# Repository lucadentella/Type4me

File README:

Type4Me

USB keyboard emulator based on PIC18f14k50.
It allows to automatically type repetitive words (passwords...)
Includes a C# GUI.

Project description on my blog:
http://www.lucadentella.it/category/type4me/

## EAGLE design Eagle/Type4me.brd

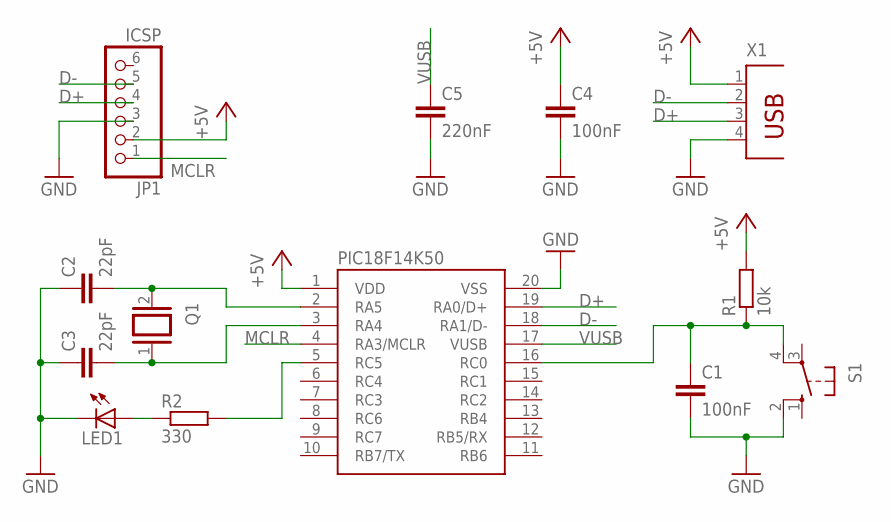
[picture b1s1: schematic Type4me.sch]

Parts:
C1, C4: 100nF; C050-030X075
C2, C3: 22pF; C025-030X050
C5: 220nF; C050-030X075
JP1: ICSP; 1X06
LED1: LED5MM
Q1: XTAL/S; QS
R1: 10k; 0207/12
R2: 330; 0207/12
S1: 10-XX; B3F-10XX
U$1: PIC18F14K50; DIP-20
X1: PN61729

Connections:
+5V: C4.1, JP1.2, R1.2, U$1.1 (VDD), X1.1
D+: JP1.4, U$1.19 (RA0/D+), X1.3
D-: JP1.5, U$1.18 (RA1/D-), X1.2
GND: C1.2, C2.1, C3.1, C4.2, C5.2, JP1.3, LED1.K (C), S1.2 (S1), U$1.20 (VSS), X1.4
MCLR: JP1.1, U$1.4 (RA3/MCLR)
unnamed: C2.2, Q1.2, U$1.2 (RA5)
unnamed: C3.2, Q1.1, U$1.3 (RA4)
unnamed: C1.1, R1.1, S1.4 (P1), U$1.16 (RC0)
unnamed: R2.2, U$1.5 (RC5)
unnamed: LED1.A, R2.1
VUSB: C5.1, U$1.17 (VUSB)

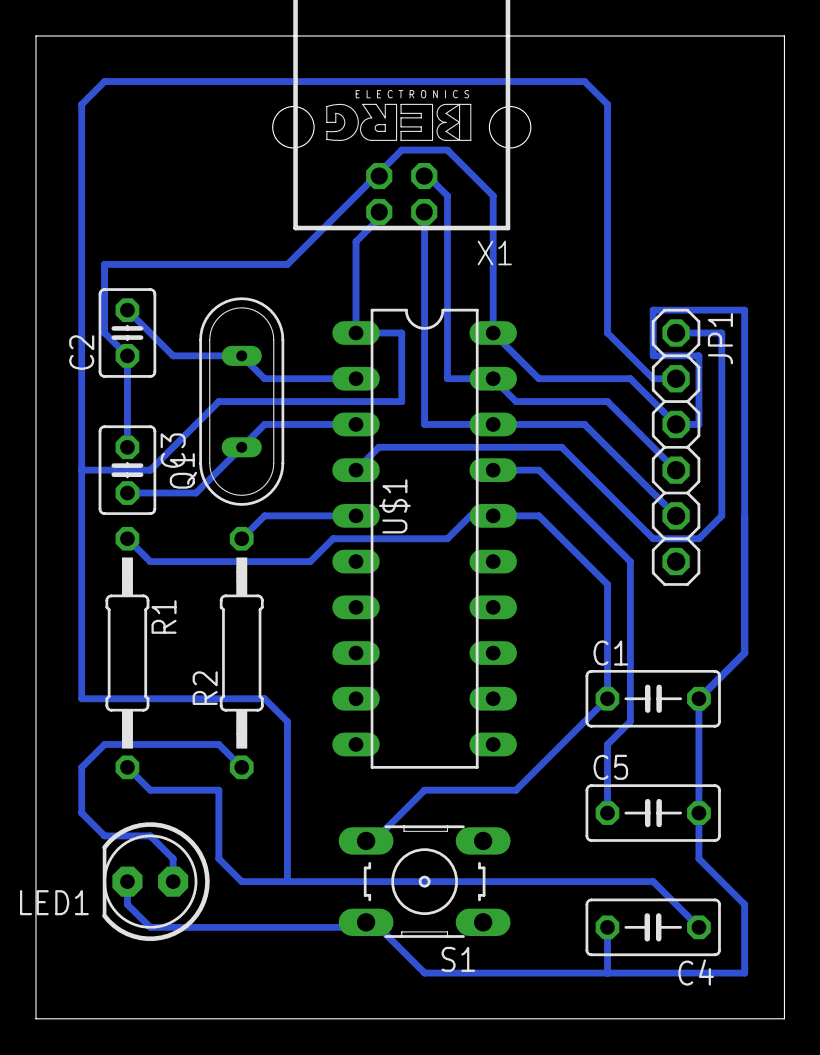
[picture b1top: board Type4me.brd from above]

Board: 2 copper layers, 41.6 x 54.6 mm, 13 parts (0 on the bottom side), 11 nets.

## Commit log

2012-10-27 first version
2013-01-09 bugfix, del key and enter command
2013-01-09 cdc driver added
2013-01-19 GUI source code added
